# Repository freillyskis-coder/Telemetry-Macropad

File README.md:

# Telemetry-Macropad
This is a place where I store all of my files for my macropad that has an accelerometer, display, and lights that will show telemetry information for racing.

### What It Does
This macropad has a computer, display, accelerometer, a few lights, and 3 keys. The accelerometer is used to measure acceleration in different directions (duh). That information gets used to display which direction it is accelerating in a traction-circle style display, or in plain number format, on the screen. The lights also indicate what direction the board is accelerating, with one pointing in each cardinal direction for the device. The lights each have two functions, requiring a long or short press. They go like this:
- Switch modes on the display (trac circle, current acceleration numbers, etc) (Short) / Set brightness (Long)
- Recalibration (Short) / Switch Units (g’s vs m/s) (Long)
- Freezes max acceleration (Short) / Reset acceleration (size of the traction circle) (Long)
  
### Why I Built This
I have seen traction circles be used in racing simulators to assist the driver. However, I had never seen one in a real car. I thought it would be really cool to try my hand at designing a device that could display information relevant to racing. In the future, I may add new features such as data collection, slip warnings, etc. 

### Challenges
I haven't done that much design work myself, so this was full of new experiences for me. I have used onshape for 3d cad work before, so it was fun learning how to use fusion (they were pretty similar, at least for what I was doing). 
I also enjoyed learning how to use the KiCAD software. I've used Rapidharness before for electrical work, but it was so cool and different designing a PCB. One of the biggest challenges was the coding, as I've only used Java for my compsci class, and figuring out how to use Github (it required a lot of youtube tutorials and headscratching). Overall, I persisted through and I gained a lot of valuable skills and had a good time!

### Designs
Schematic            |  PCB         |   Case    |   
:-------------------------:|:-------------------------:|:-------------------------:|
  |    |   

# Overall Hackpad:

### Bill Of Materials

- [4 x SK6812MINI-E](https://www.digikey.com/en/products/detail/adafruit-industries-llc/4960/14302512?gclsrc=aw.ds&gad_source=1&gad_campaignid=20228387720&gbraid=0AAAAADrbLlgqid9MNTrAWhJKMXZF-C39b&gclid=CjwKCAiAzZ_NBhAEEiwAMtqKyy2T8yJqQVE5hG_iRolQtgHnV_oXdoksU0azACau9GJ1NhhwS3yk6hoCPRcQAvD_BwE) - lights, $2.95
- [1 x XIAO RP2040 DIP](https://www.seeedstudio.com/XIAO-RP2040-v1-0-p-5026.html) - computer, $3.99
- [3 x Cherry MX Switches](https://mechanicalkeyboards.com/products/cherry-mx2a-silent-red-45g-linear?variant=48014625177900) - switches $0.40
- [3 x DSA Black Keycaps](https://thepihut.com/products/black-dsa-keycaps-for-mx-compatible-switches-10-pack) - keycaps (10 pack) $5.80
- [4 x M3x3mm heatset inserts](https://www.adafruit.com/product/4256) - inserts, $5.95 
- [4 x M3x10mm screws](https://www.amazon.com/Screws-Assortment-Machine-Washers-Phillips/dp/B0G9HDWD3K/ref=sr_1_12?crid=15VO2HWVHE0U2&dib=eyJ2IjoiMSJ9.WV9vbUoR7v5KPi58AH83sZsSA7HvHG40hEXMA8HbueS60EWGKL47-TZYQY3TXXlaLUiDxuMThePG_C0DW73KA63eM30HCJDZl3elUEXfaLVWdxwIaKEVdZeLDRrm8IMZwNt0g-c5EK8s48QIQ1roqfLd_2wHsQgpIbIy9LAY3n9HKYXzYhvnC8PRo9urp8rpHIZFLXKtcY7svDHuq47DynBfwkhPvRxjzr1DQoavsg9FY-STt1nrAQnZTKOSEv1by2L08LQVAFx4QCqLNYtsLBaGEWl_z5qazF4EEkFyGn0.bwl7yN3XZuO-iIm4WUgd6dJ_ZpySQU-Q4Z4oi7Gi01I&dib_tag=se&keywords=M3%2Bscrews&qid=1774370715&s=industrial&sprefix=m3%2Bscrew%2Cindustrial%2C140&sr=1-12&th=1)   - screws, $3.99
- My PCB, printed
- My 3D printed case

I have an accelerometer and 0.96" display in my designs, but I am not requesting them as I know it they not a part of the kit. I will pay for this myself.
- [1 x MPU 6050](https://www.alibaba.com/product-detail/TZT-1Set-IIC-I2C-GY-521_1600855862949.html?spm=a2700.prosearch.normal_offer.d_title.444e67afTjlFTW&priceId=fc64e04c517543e99b5e70350475b235) - accelerometer, $1.45
- [1 x SSD1306 OLED](https://www.alibaba.com/product-detail/0-96-128x64-I2C-IIC-Serial_1601221974195.html?spm=a2700.prosearch.normal_offer.d_title.713e67af2h8ats&selectedCarrierCode=SEMI_MANAGED_STANDARD%40%40STANDARD&priceId=9263331f4c5146ce9335b75a9e5a434e) - display, $2.50

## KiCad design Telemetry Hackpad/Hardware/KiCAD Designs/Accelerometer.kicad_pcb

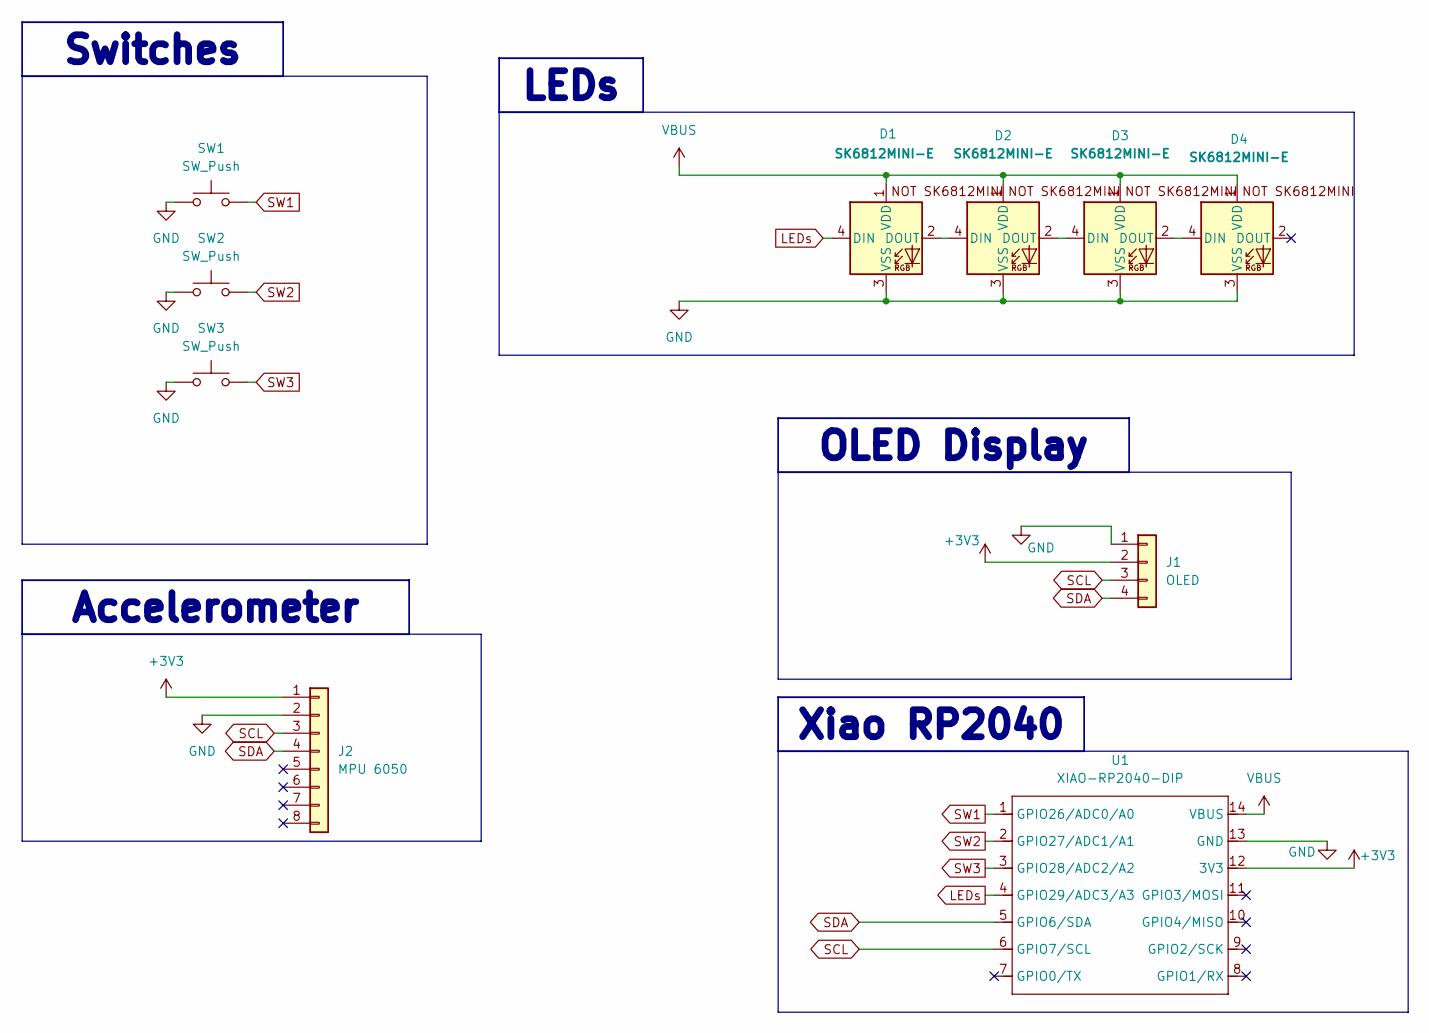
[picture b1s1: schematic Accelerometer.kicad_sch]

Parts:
D1, D2, D3, D4: SK6812MINI-E; SK6812MINI-E_fixed
J1: OLED; PinHeader_1x04_P2.54mm_Vertical
J2: MPU 6050; PinHeader_1x08_P2.54mm_Vertical
SW1, SW2, SW3: SW_Push; SW_Cherry_MX_1.00u_PCB
U1: XIAO-RP2040-DIP; XIAO-RP2040-SMD

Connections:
+3V3: J1.2 (VDD), J2.1 (VCC), U1.12 (3V3)
GND: D1.3 (VSS), D2.3 (VSS), D3.3 (VSS), D4.3 (VSS), J1.1 (GND), J2.2 (GND), SW1.1, SW2.1, SW3.1, U1.13 (GND)
LEDs: D1.4 (DIN), U1.4 (GPIO29/ADC3/A3)
unnamed: D1.2 (DOUT), D2.4 (DIN)
unnamed: D2.2 (DOUT), D3.4 (DIN)
unnamed: D3.2 (DOUT), D4.4 (DIN)
SCL: J1.3 (SCL), J2.3 (SCL), U1.6 (GPIO7/SCL)
SDA: J1.4 (SDA), J2.4 (SDA), U1.5 (GPIO6/SDA)
SW1: SW1.2, U1.1 (GPIO26/ADC0/A0)
SW2: SW2.2, U1.2 (GPIO27/ADC1/A1)
SW3: SW3.2, U1.3 (GPIO28/ADC2/A2)
VBUS: D1.1 (VDD), D2.1 (VDD), D3.1 (VDD), D4.1 (VDD), U1.14 (VBUS)

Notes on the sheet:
Accelerometer
LEDs
Xiao RP2040
Switches
OLED Display

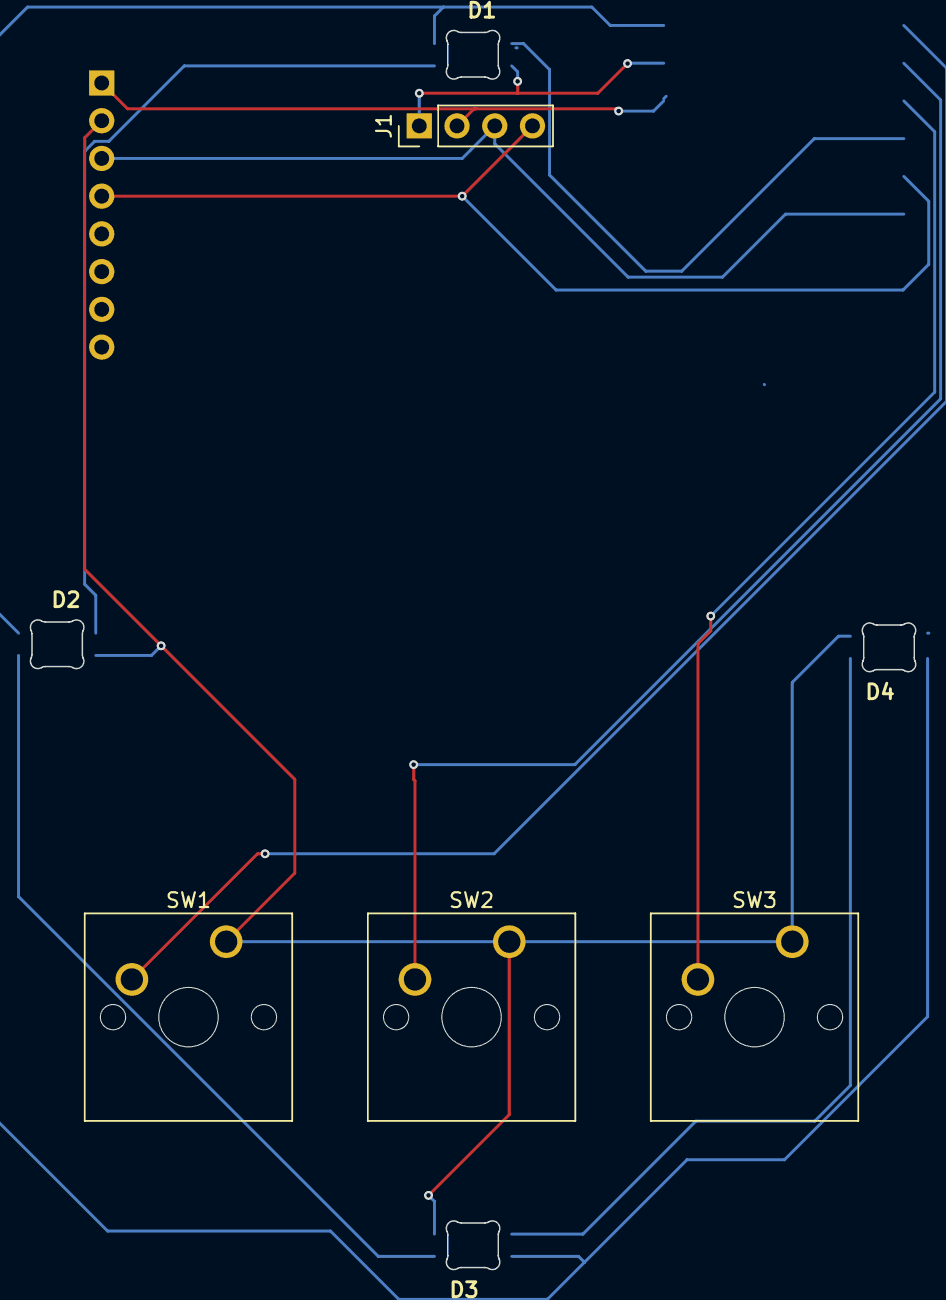
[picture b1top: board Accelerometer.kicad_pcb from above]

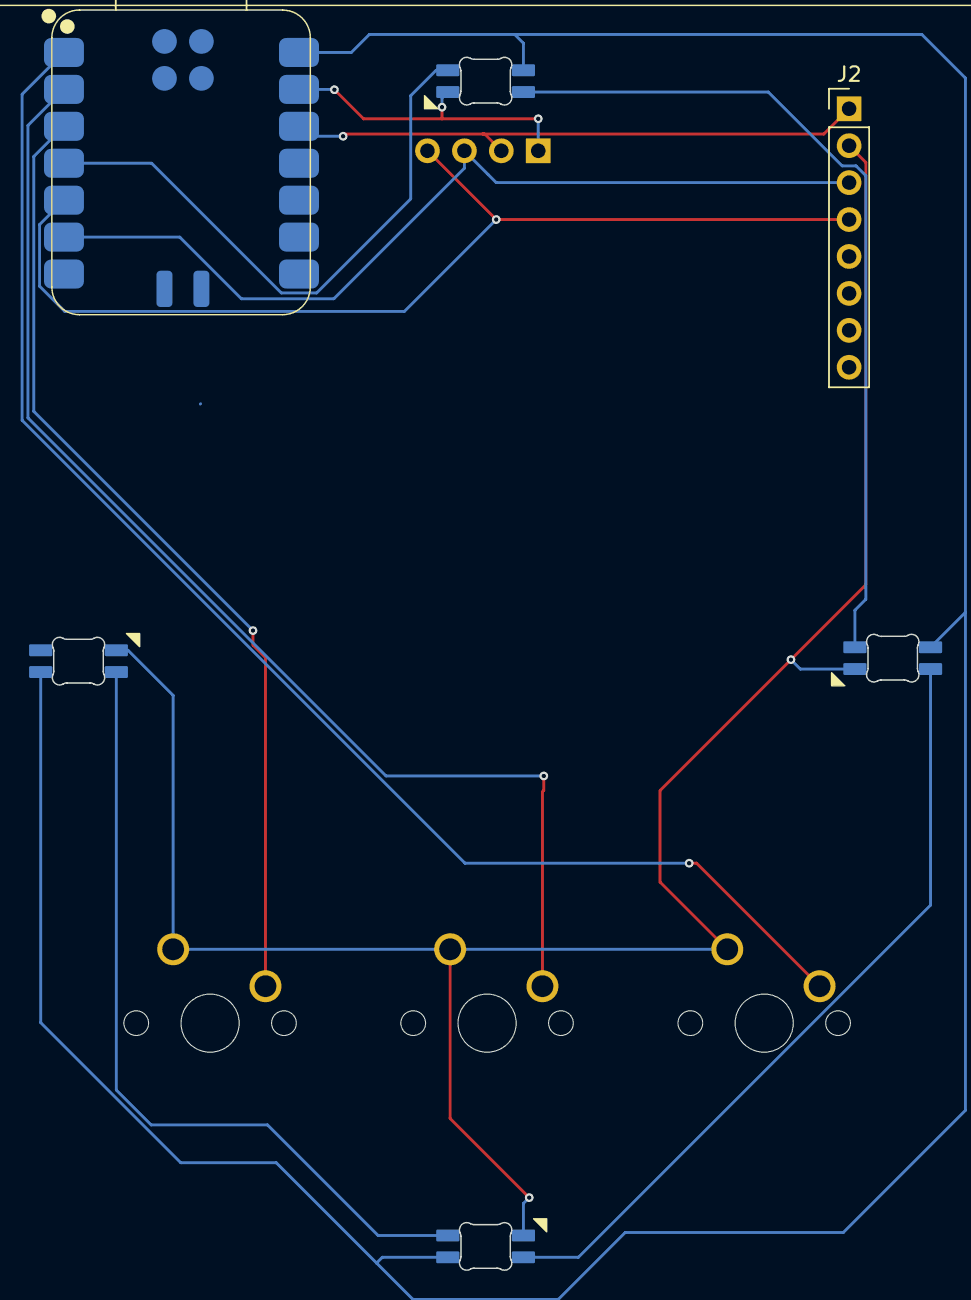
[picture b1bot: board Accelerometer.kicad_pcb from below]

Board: 2 copper layers, 59.6 x 83.4 mm, 10 parts (2 on the bottom side), 12 nets.

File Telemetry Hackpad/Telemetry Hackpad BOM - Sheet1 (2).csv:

Part,Cost,Link
SSD1306 OLED - display,$2.50,https://www.alibaba.com/product-detail/0-96-128x64-I2C-IIC-S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
4 x SK6812MINI-E - lights,$2.95,https://www.digikey.com/en/products/detail/adafruit-industri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
XIAO RP2040 DIP - computer,$3.99,https://www.seeedstudio.com/XIAO-RP2040-v1-0-p-5026.html
3 x Cherry MX Switches - switches,$0.40,https://mechanicalkeyboards.com/products/cherry-mx2a-silent-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
3 x DSA Black Keycaps - keycaps (10 pack),$5.80,https://thepihut.com/products/black-dsa-keycaps-for-mx-compa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
4 x M3x3mm heatset inserts,$5.95,https://www.adafruit.com/product/4256
4 x M3x10mm screws - screws,$3.99,https://www.amazon.com/Screws-Assortment-Machine-Washers-Phi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
"My PCB, printed",,
My 3D printed case,,
,,
Total:,$25.58,
,,
I will purchase the accelerometer myself,,
MPU 6050 - accelerometer,$1.45,https://www.alibaba.com/product-detail/TZT-1Set-IIC-I2C-GY-5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

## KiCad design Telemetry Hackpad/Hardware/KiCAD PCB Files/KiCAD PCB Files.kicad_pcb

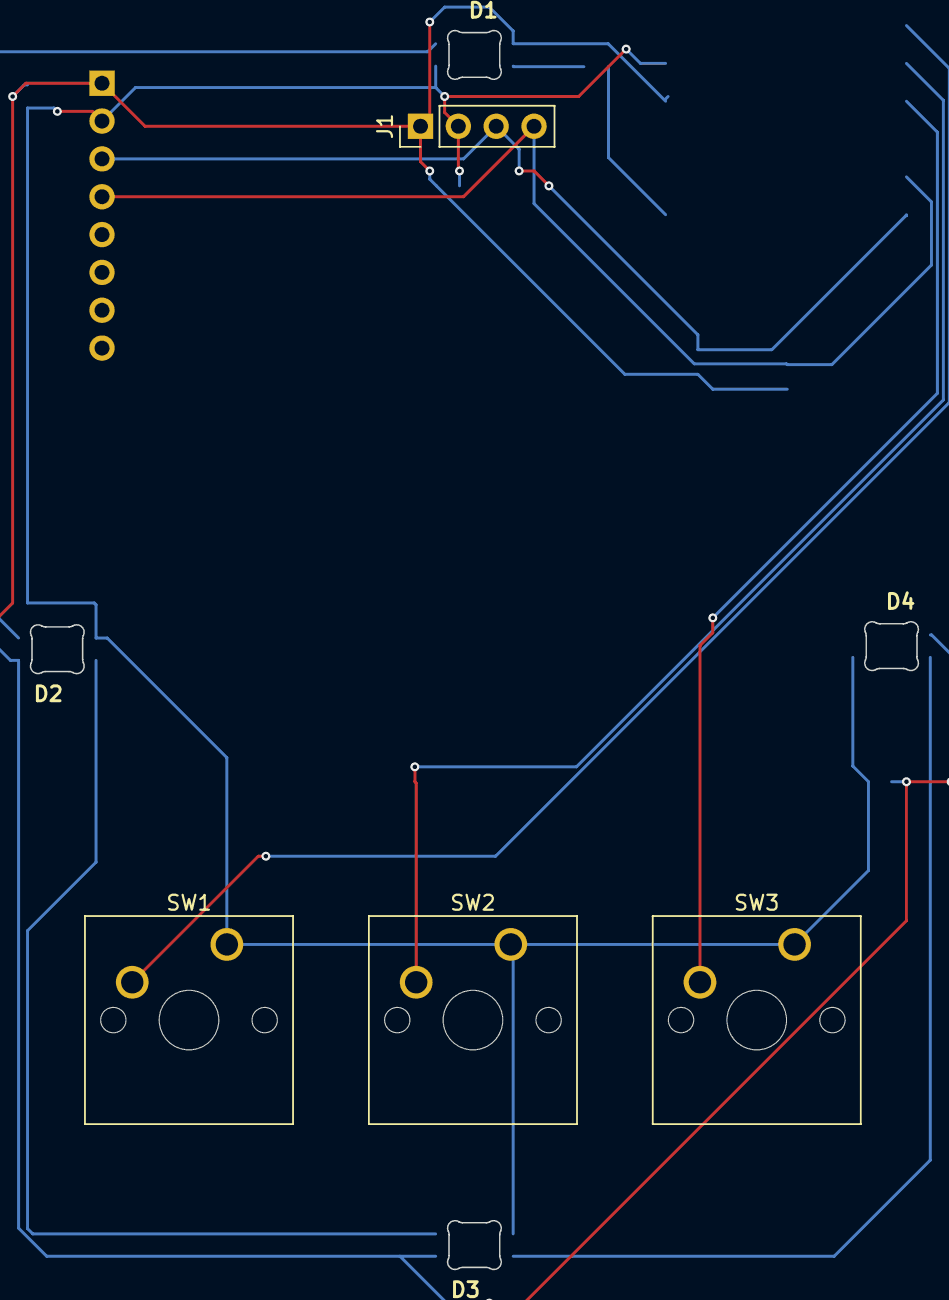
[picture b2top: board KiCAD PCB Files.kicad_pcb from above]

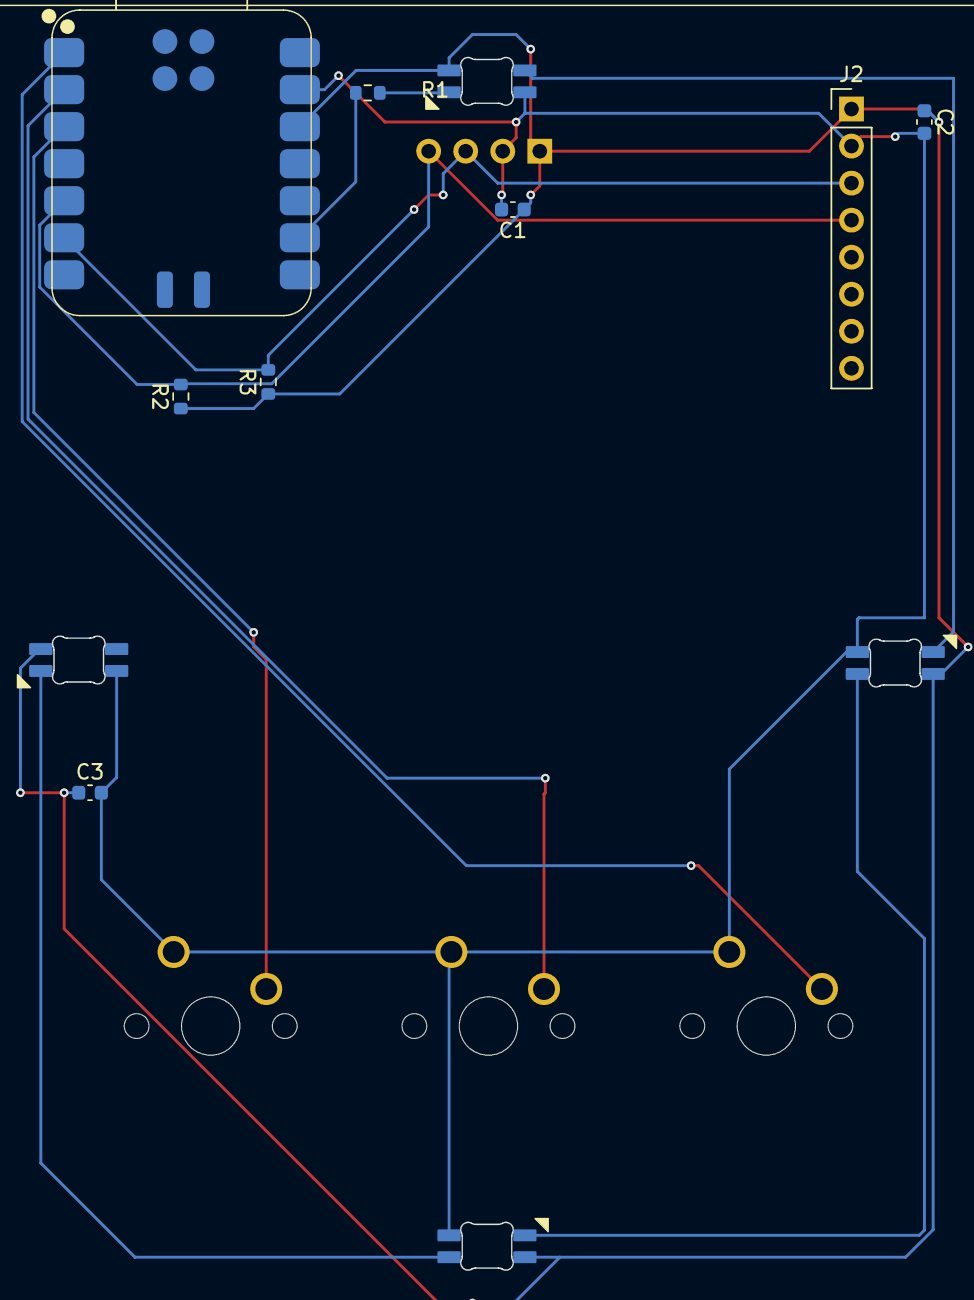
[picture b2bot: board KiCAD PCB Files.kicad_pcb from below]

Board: 2 copper layers, 59.6 x 83.2 mm, 16 parts (8 on the bottom side), 12 nets.

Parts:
C1, C2: 0.1uF; C_0603_1608Metric
C3: 47uF; C_0603_1608Metric
D1, D2, D3, D4: SK6812MINI-E; SK6812MINI-E_fixed (1)
J1: OLED; PinHeader_1x04_P2.54mm_Vertical
J2: MPU 6050; PinHeader_1x08_P2.54mm_Vertical
R1: 330Ω; R_0603_1608Metric
R2, R3: 4.7k; R_0603_1608Metric
SW1, SW2, SW3: SW_Push; SW_Cherry_MX_1.00u_PCB
U1: XIAO-RP2040-DIP; XIAO-RP2040-SMD

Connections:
3V3: C1.1, C2.1, C3.1, D1.4 (VDD), D2.4 (VDD), D3.4 (VDD), D4.4 (VDD), J1.1 (VCC), J2.1 (VCC), R2.1, R3.1, U1.12 (3V3)
/GND: C1.2, C2.2, C3.2, D1.2 (VSS), D2.2 (VSS), D3.2 (VSS), D4.2 (VSS), J1.2 (GND), J2.2 (GND), SW1.1, SW2.1, SW3.1, U1.13 (GND)
/SCL: J1.3 (SCL), J2.3 (SCL), R3.2, U1.6 (GPIO7/SCL)
/SDA: J1.4 (SDA), J2.4 (SDA), R2.2, U1.5 (GPIO6/SDA)
unnamed: D1.3 (DIN), R1.1
unnamed: D1.1 (DOUT), D2.3 (DIN)
unnamed: D2.1 (DOUT), D3.3 (DIN)
unnamed: D3.1 (DOUT), D4.3 (DIN)
unnamed: R1.2, U1.9 (GPIO2/SCK)
unnamed: SW1.2, U1.1 (GPIO26/ADC0/A0)
unnamed: SW2.2, U1.2 (GPIO27/ADC1/A1)
unnamed: SW3.2, U1.3 (GPIO28/ADC2/A2)

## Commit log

2026-03-24 Added all macropad files
2026-03-24 Rename KiCAD PCB.png to KiCAD_PCB.png
2026-03-24 Rename KiCAD Schematic.png to KiCAD_Schematic.png
2026-03-24 Rename Complete Side View.png to Complete_Side_View.png
2026-03-24 Update README.md to include a description
2026-03-24 Update README.md BOM to correctly link the items
2026-03-24 Added the correct KiCAD files
2026-03-24 Hopefully these are the correct files
    I believe that, before uploading my KiCAD schematic and PCB files, in trying to change the name of the project, I accidentally messed up the linking between them or something. However, I believe that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
2026-03-25 Added new and improved KiCAD Schematic
    Updated by vmshade, another hackclubber who I met on the slack
2026-03-25 Update README.md to include BOM pricing
2026-03-25 Added all complete files for my KiCAD designs
2026-03-25 Update README.md to include a "Why I built This" section
2026-03-29 Added files to repository
2026-03-29 Removed SK6812MINI-E footrpints/symbols
2026-04-06 Adding files
2026-04-06 Adding last files
2026-04-07 Correct images and indicate that I am not requesting an MPU 6050 acclerometer
2026-04-07 Rearranged files
2026-04-09 Added production folders
    Moved items around and added shipping routes for various files
